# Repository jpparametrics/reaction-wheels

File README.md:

# THIS REPO IS NO LONGER USED. CHECK ORESAT-STRUCTURE REPO FOR CURRENT REACTION WHEEL FILES
# CubeSAT-Reaction-Wheel

Portland State University is developing Oregon’s first orbital satellite, a 2U Cubesat dubbed Oresat. This cubesat will use a reaction wheel system for attitude control and pointing of the onboard antennas and cameras. I am developing the controller, designing the structure and sourcing hardware for both the space rated system and a ground test system that will also be used for demonstration purposes. This system has been tested using the Dryden Drop Tower at PSU as well as in captive hanging tests. The current controller is a simple proportional controller, however using data collected from the drop test I will refine the model and implement a more sophisticated controller. Video of the tests can be seen at:  [Captive Controller Hanging Test](https://www.youtube.com/watch?v=Is1gPHlewtgand) and [Dryden Drop Tower Micro-Gravity Test](https://www.youtube.com/watch?v=cC2FpmCP5B4)

Both of the previous tests were conducted using a simple open loop proportional controller that was tuned via test to induce a slightly underdamped response. This was to create data that can be more easily compared to an ideal model.

## Ongoing Development

There's a Google drive folder [here](https://drive.google.com/drive/folders/0BzW5XSZ87m-TVnFDZUc1TUkwN1U?usp=sharing)

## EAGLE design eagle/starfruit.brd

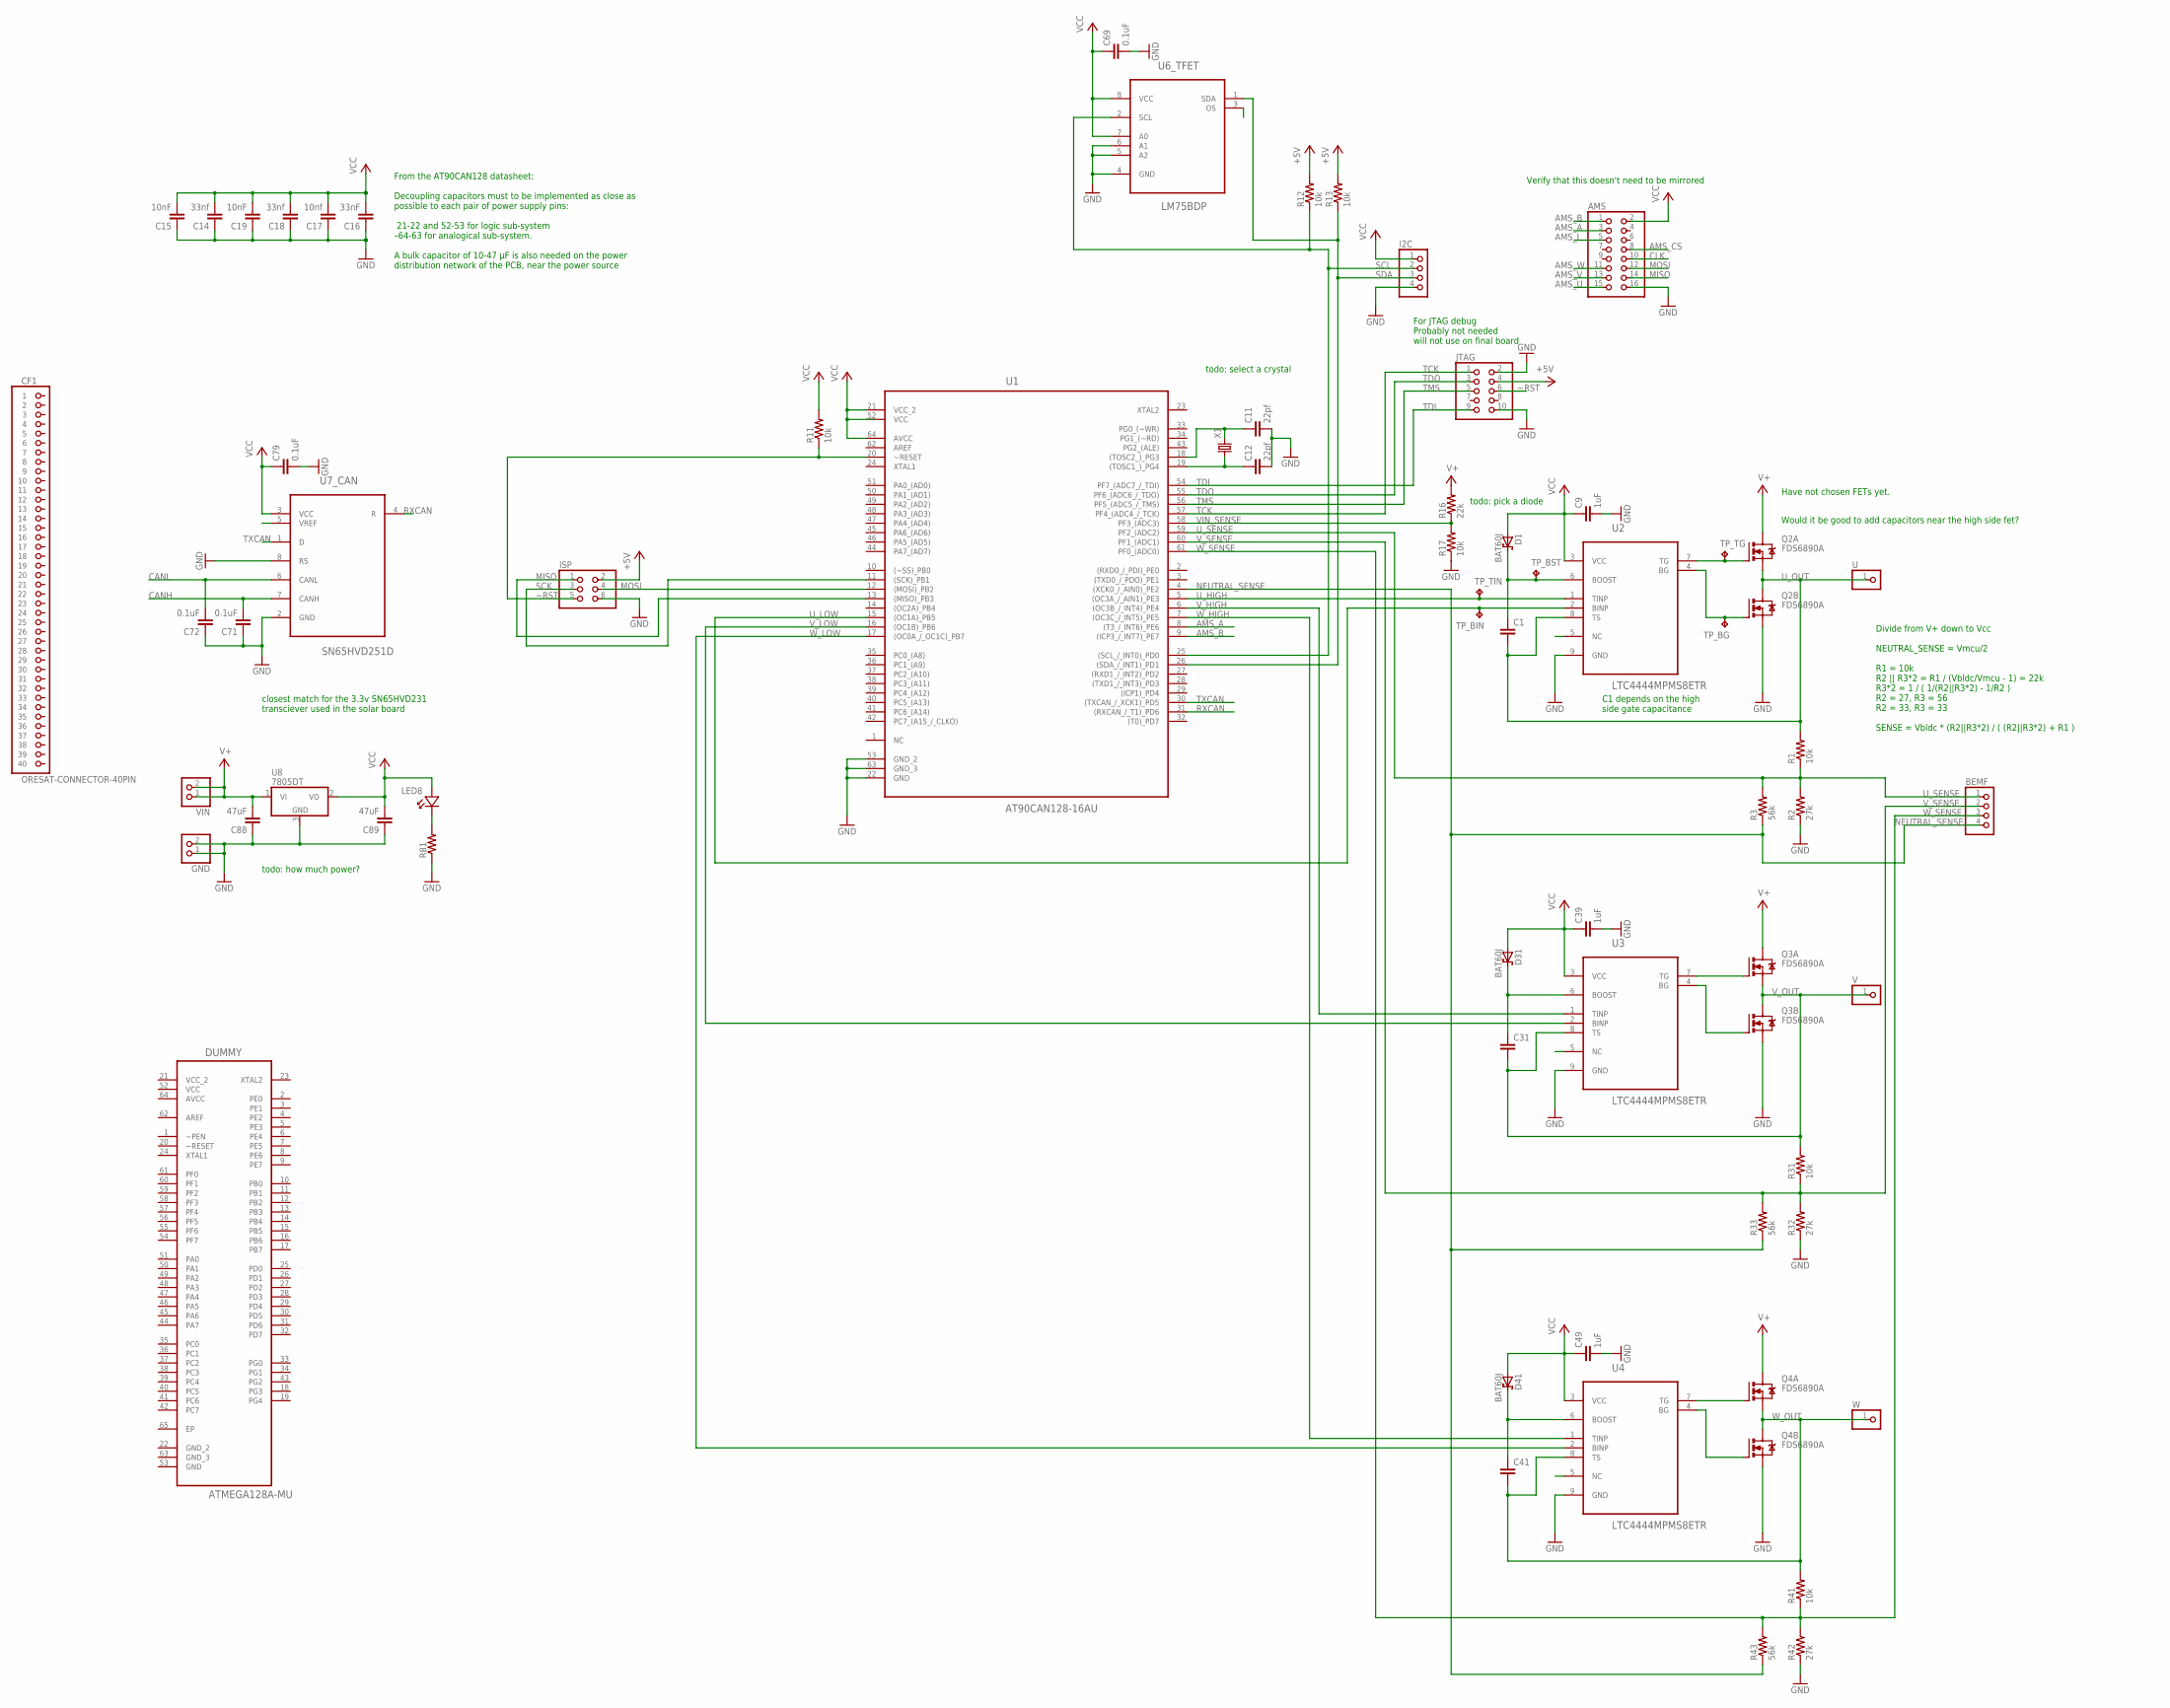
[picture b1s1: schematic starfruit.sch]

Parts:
AMS: PINHD-2X8; 2X08
BEMF: PINHD-1X4; 1X04
C1, C31, C41: C-EU0603-B-NOSILK; .0603-B-NOSILK
C9, C39, C49: 1uF; .0603-B-NOSILK
C11, C12: 22pf; .0603-B-NOSILK
C14, C18: 33nf; .0603-B-NOSILK
C15, C19: 10nF; .0603-B-NOSILK
C16: 33nF; .0603-B-NOSILK
C17: 10nf; .0603-B-NOSILK
C69, C71, C72, C79: 0.1uF; .0603-B-NOSILK
C88, C89: 47uF; .0603-B-NOSILK
CF1: ORESAT-CONNECTOR-40PIN; HARWIN-ARCHER-M50-3202045
D1, D31, D41: BAT60J; SOD323_ST
DUMMY: ATMEGA128A-MU; QFN50P900X900X100-65N
GND: PINHD-1X2; 1X02
I2C: PINHD-1X4; 1X04
ISP: PINHD-2X3; 2X03
JTAG: PINHD-2X5; 2X05
LED8: LED-0603
Q2, Q3, Q4: FDS6890A; M08A
R1, R11, R12, R13, R17, R31, R41: 10k; .0603-B-NOSILK
R2, R32, R42: 27k; .0603-B-NOSILK
R3, R33, R43: 56k; .0603-B-NOSILK
R16: 22k; .0603-B-NOSILK
R81: R-US_0603-B-NOSILK; .0603-B-NOSILK
TP_BG: TPTP06R; TP06R
TP_BIN: TPTP06R; TP06R
TP_BST: TPTP06R; TP06R
TP_TG: TPTP06R; TP06R
TP_TIN: TPTP06R; TP06R
U: PINHD-1X1; 1X01
U1: AT90CAN128-16AU; QFP80P1600X1600X120-64N
U2, U3, U4: LTC4444MPMS8ETR; SOP65P490X110-9N
U6_TFET: LM75BDP; SOP65P490X110-8N
U7_CAN: SN65HVD251D; SOIC127P600X175-8N
U8: 7805DT; TO252
V: PINHD-1X1; 1X01
VIN: PINHD-1X2; 1X02
W: PINHD-1X1; 1X01
X1: CRYSTALCTS406; CTS406

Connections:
AMS_A: AMS.3, U1.8 ((T3_/_INT6)_PE6)
AMS_B: AMS.1, U1.9 ((ICP3_/_INT7)_PE7)
AMS_CS: AMS.8
AMS_I: AMS.5
AMS_U: AMS.15
AMS_V: AMS.13
AMS_W: AMS.11
AVCC: DUMMY.64 (AVCC)
C79: C79.2
CANH: C71.2, U7_CAN.7 (CANH)
CANL: C72.2, U7_CAN.6 (CANL)
CLK: AMS.10
GND: AMS.16, C9.2, C11.2, C12.2, C14.1, C15.1, C16.1, C17.1, C18.1, C19.1, C39.2, C49.2, C69.2, C71.1, C72.1, C88.1, C89.1, GND.1, GND.2, I2C.4, ISP.6, JTAG.2, JTAG.10, Q2.3 (S), Q3.3 (S), Q4.3 (S), R2.1, R17.1, R32.1, R42.1, R81.1, U1.22 (GND), U1.53 (GND_2), U1.63 (GND_3), U2.9 (GND), U3.9 (GND), U4.9 (GND), U6_TFET.4 (GND), U6_TFET.5 (A2), U6_TFET.6 (A1), U7_CAN.2 (GND), U7_CAN.8 (RS), U8.3 (GND)
MISO: AMS.14, ISP.1, U1.13 ((MISO)_PB3)
MOSI: AMS.12, ISP.4, U1.12 ((MOSI)_PB2)
unnamed: LED8.K, R81.2
NEUTRAL_SENSE: BEMF.4, R3.1, R33.1, R43.1, U1.4 ((XCK0_/_AIN0)_PE2)
RXCAN: U1.31 ((RXCAN_/_T1)_PD6), U7_CAN.4 (R)
SCK: ISP.3, U1.11 ((SCK)_PB1)
SCL: I2C.2, R12.1, U1.25 ((SCL_/_INT0)_PD0), U6_TFET.2 (SCL)
SDA: I2C.3, R13.1, U1.26 ((SDA_/_INT1)_PD1), U6_TFET.1 (SDA)
TCK: JTAG.1, U1.57 (PF4_(ADC4_/_TCK))
TDI: JTAG.9, U1.54 (PF7_(ADC7_/_TDI))
TDO: JTAG.3, U1.55 (PF6_(ADC6_/_TDO))
TMS: JTAG.5, U1.56 (PF5_(ADC5_/_TMS))
TOSC1: C12.1, U1.19 ((TOSC1_)_PG4), X1.1
TOSC2: C11.1, U1.18 ((TOSC2_)_PG3), X1.3 (2)
TXCAN: U1.30 ((TXCAN_/_XCK1)_PD5), U7_CAN.1 (D)
T_BG: Q3.4 (G), U3.4 (BG)
U2_BOOST: C1.1, D1.C, TP_BST.TP, U2.6 (BOOST)
U2_NC: U2.5 (NC)
U3_BOOST: C31.1, D31.C, U3.6 (BOOST)
U3_NC: U3.5 (NC)
U4_BOOST: C41.1, D41.C, U4.6 (BOOST)
U4_NC: U4.5 (NC)
U6_NC: U6_TFET.3 (OS)
U7_NC: U7_CAN.5 (VREF)
U_BG: Q2.4 (G), TP_BG.TP, U2.4 (BG)
U_HIGH: TP_TIN.TP, U1.5 ((OC3A_/_AIN1)_PE3), U2.1 (TINP)
U_LOW: TP_BIN.TP, U1.15 ((OC1A)_PB5), U2.2 (BINP)
U_OUT: C1.2, Q2.1 (S), Q2.5 (D), Q2.6 (D), R1.2, U.1, U2.8 (TS)
U_SENSE: BEMF.1, R1.1, R2.2, R3.2, U1.59 (PF2_(ADC2))
U_TG: Q2.2 (G), TP_TG.TP, U2.7 (TG)
V+: C88.2, Q2.7 (D), Q2.8 (D), Q3.7 (D), Q3.8 (D), Q4.7 (D), Q4.8 (D), R16.2, U8.1 (VI), VIN.1, VIN.2
VCC: AMS.2, C9.1, C14.2, C15.2, C16.2, C17.2, C18.2, C19.2, C39.1, C49.1, C69.1, C79.1, C89.2, D1.A, D31.A, D41.A, DUMMY.52 (VCC), I2C.1, ISP.2, JTAG.4, LED8.A, R11.2, R12.2, R13.2, U1.21 (VCC_2), U1.52 (VCC), U1.64 (AVCC), U2.3 (VCC), U3.3 (VCC), U4.3 (VCC), U6_TFET.7 (A0), U6_TFET.8 (VCC), U7_CAN.3 (VCC), U8.2 (VO)
VCC_2: DUMMY.21 (VCC_2)
VIN_SENSE: R16.1, R17.2, U1.58 (PF3_(ADC3))
V_HIGH: U1.6 ((OC3B_/_INT4)_PE4), U3.1 (TINP)
V_LOW: U1.16 ((OC1B)_PB6), U3.2 (BINP)
V_OUT: C31.2, Q3.1 (S), Q3.5 (D), Q3.6 (D), R31.2, U3.8 (TS), V.1
V_SENSE: BEMF.2, R31.1, R32.2, R33.2, U1.60 (PF1_(ADC1))
V_TG: Q3.2 (G), U3.7 (TG)
W_BG: Q4.4 (G), U4.4 (BG)
W_HIGH: U1.7 ((OC3C_/_INT5)_PE5), U4.1 (TINP)
W_LOW: U1.17 ((OC0A_/_OC1C)_PB7), U4.2 (BINP)
W_OUT: C41.2, Q4.1 (S), Q4.5 (D), Q4.6 (D), R41.2, U4.8 (TS), W.1
W_SENSE: BEMF.3, R41.1, R42.2, R43.2, U1.61 (PF0_(ADC0))
W_TG: Q4.2 (G), U4.7 (TG)
~RST: ISP.5, JTAG.6, R11.1, U1.20 (~RESET)

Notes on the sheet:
From the AT90CAN128 datasheet: Decoupling capacitors must to be implemented as close as possible to each pair of power supply pins: 21-22 and 52-53 for logic sub-system –64-63 for analogical sub-system. A bulk capacitor of 10-47 µF is also needed on the power distribution network of the PCB, near t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
Divide from V+ down to Vcc NEUTRAL_SENSE = Vmcu/2 R1 = 10k R2 || R3*2 = R1 / (Vbldc/Vmcu - 1) = 22k R3*2 = 1 / ( 1/(R2||R3*2) - 1/R2 ) R2 = 27, R3 = 56 R2 = 33, R3 = 33 SENSE = Vbldc * (R2||R3*2) / ( (R2||R3*2) + R1 )
For JTAG debug Probably not needed will not use on final board
C1 depends on the high side gate capacitance
Have not chosen FETs yet.
Verify that this doesn't need to be mirrored
closest match for the 3.3v SN65HVD231 transciever used in the solar board
todo: select a crystal
todo: how much power?
Would it be good to add capacitors near the high side fet?
todo: pick a diode

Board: 2 copper layers, 67 parts (0 on the bottom side), 45 nets, no tracks yet.

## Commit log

2016-06-08 fixed link
2016-06-08 really fixed link
2016-06-15 adding future works
2016-06-17 updated knowledge base for newbs
2016-08-14 updated some figures
2016-08-16 added time lapse
2016-08-16 LaTeX'd the FBD
2016-08-16 fixed axes
2016-08-17 changes to figures, rewrote introduction,results, and acknowlegements sections
2016-08-17 a few small textual changes
2016-08-17 a few _more_ small textual changes
2016-08-18 more edits, final version or close to it.
2016-08-18 final batch of changes to the paper, may god have mercy on our souls
2016-08-18 fixed a few lingering typos
2016-08-18 added attribution
2016-08-18 removed 'finally'
2016-08-18 few more grammatical corrections, ugh
2016-09-06 added AIAA Space 2016 poster
2016-09-06 new layout for the poster
2016-09-06 some cosmetic changes
2016-09-07 landscape...uhg
2016-09-12 final version of poster (landscape)
2016-09-12 few small last minute layout changes
2016-10-15 create a space to share jupyter notebooks
2016-10-15 convert units to Nm, change minimum orbit assumption from from 200 to 330km
2016-10-15 expanded a bit on torques
2016-10-21 solidworks model for AMS eval board
2016-10-28 layout
2016-10-29 Link to Google Drive
2018-05-08 prototype of reaction wheel mounting
2018-05-09 prototyping for the D1104... then SW crashed
2018-05-09 finished draft of encoder board for D1104
2018-05-10 fancified the motor mount
2018-05-10 extended board further; fixed CSK holes on wedge
2018-05-29 other-handed version of the wedge
2018-06-07 tweaked wedge to work with structure
2018-06-07 more uniform assembly scheme
2018-06-10 added materials for calculating CoM
2018-06-10 intermediate mounting scheme for reaciton wheels
    A small C-beam mounts to the structure and the wedges mount to the beam.
    This allows us to tweak the position -- and the entire mounting scheme
    -- of the reaction wheels without needing to re-machine the entire
    structure!
2018-06-11 tweaked wedge locations to symmetrize encoders
2018-07-30 approximate details of motor model based on their drawing
2018-07-30 new revision of the reaction wheels; needs tweaking
2018-08-13 removed files from previous revision
2018-08-13 renamed things for new revision appropriately
2018-08-13 updated mounting beam assembly
2018-08-13 wonky double wheel unit...? (got rid of it)
2018-09-02 re-tweaked wheel and cage dimensions
2018-09-02 made the cage shear-able
2018-09-02 optimized to fit in 3 slots; materials and colors
2018-09-16 created technical drawing of the reaction wheel
2018-09-23 finalized ACS board and provided DXF/drawing
2018-10-07 added thermal contacts to the ACS board
2018-12-03 updated mounting beam
2019-02-25 fixed shoulder screw, mounting beam discrepancies
2019-02-25 setup the example structure to be used for RW demo
2019-02-25 added recent tweaks to the encoder board drawing
2019-02-25 alignment tweaks on RW and cap
2019-02-25 added missing fasteners; encoder board DXF
2019-08-20 "auto-generated from update_repos.py"
2019-09-24 Update README.md
    Updated to state that this repo is no longer used
